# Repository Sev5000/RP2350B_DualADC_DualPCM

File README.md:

# RP2350B_DualADC_DualPCM
This is a PCB to neatly package a RP2350B, two AD9226 ADC PCBs and two PCM1802 audio boards for capture with hsdaoh.
Specifically designed to still be usefull without smds (no head switch input then). Through-hole soldering only works just fine.

For use with [https://github.com/steve-m/hsdaoh-rp2350/tree/pcm1802](https://github.com/steve-m/hsdaoh/tree/dual_12bit_adc)

Features:
- Two 12bit 40MS/s ADCs
- Four channel audio input all with a common clock
- No SMD soldering needed! Works fine just connecting breakout boards
- Socket for a Pimoroni PGA2350 and RP2350 and its periphery
- The protected head switch input has footprints for edge and horizontal SMA/SMB (SMD soldering needed)
- Socket for USB C and Micro B breakouts

Bill of material: 
- 1x This PCB (Send the Gerber .zip to JLC, PCBWay, ..)
- 1x Pimoroni PGA2350
- 2x AD9226: https://aliexpress.com/item/1005003038271519.html
- 2x PCM1802: https://aliexpress.com/item/1005006412873984.html
- 4x RCA-105 or RCA-106: https://aliexpress.com/item/1005006152724809.html
- 2x 9pin 2.54mm pin-socket header 
- 2x 2x10pin 2.54mm pin-socket header
- 2x 3pin 2.54mm pin header (remove the center pin for connecting R/L of the PCM1802)
- 2x 3pin 2.54mm pin-socket header (remove the center pin for connecting R/L of the PCM1802)
- 1x vertical 6mm push button: https://aliexpress.com/item/1005005831153897.html (horizontal soldered in vertical and a drop of glue for stability works as well)

No SMD variant:
- 1x Adafruit DVI breakout board
- 4x 2x8pin 2.54mm pin-socket header
- Either Adafruit USB Micro-B Breakout Board or Adafruit USB C Breakout Board

SMD Variant with PGA2350:
- Regular HDMI connector
- micro USB connector
- 8× 0402 270 ohm resistors
- 4x 0805 100nF ceramic capacitors
- For experimental EDID communication and HPD: 4x SOD123 3.3V Zener, 4x 0402 ~27 ohm resistors, 2x 0402 2k2 ohm resistors

For head switch input:
- 1x SOD123 3.3V zener diode
- 1x SOD123 standard diode
- 1x 0805 1k resistor
- 1x edge SMA/SMB or horizontal SMA/SMB and/or 2pin header

Notes:
- Soldering the RP2350B and its periphery might work but was not tested so far.
- The PCM1802 board needs MODE0 (MODE1 only with previous HSDAOH releases) bridged *and* connected to 3.3V with a wire (Those boards have a design error):
NOTE: Picture shows the configuration for the older firmware, now only MODE0 needs to be bridged and connected to 3.3V

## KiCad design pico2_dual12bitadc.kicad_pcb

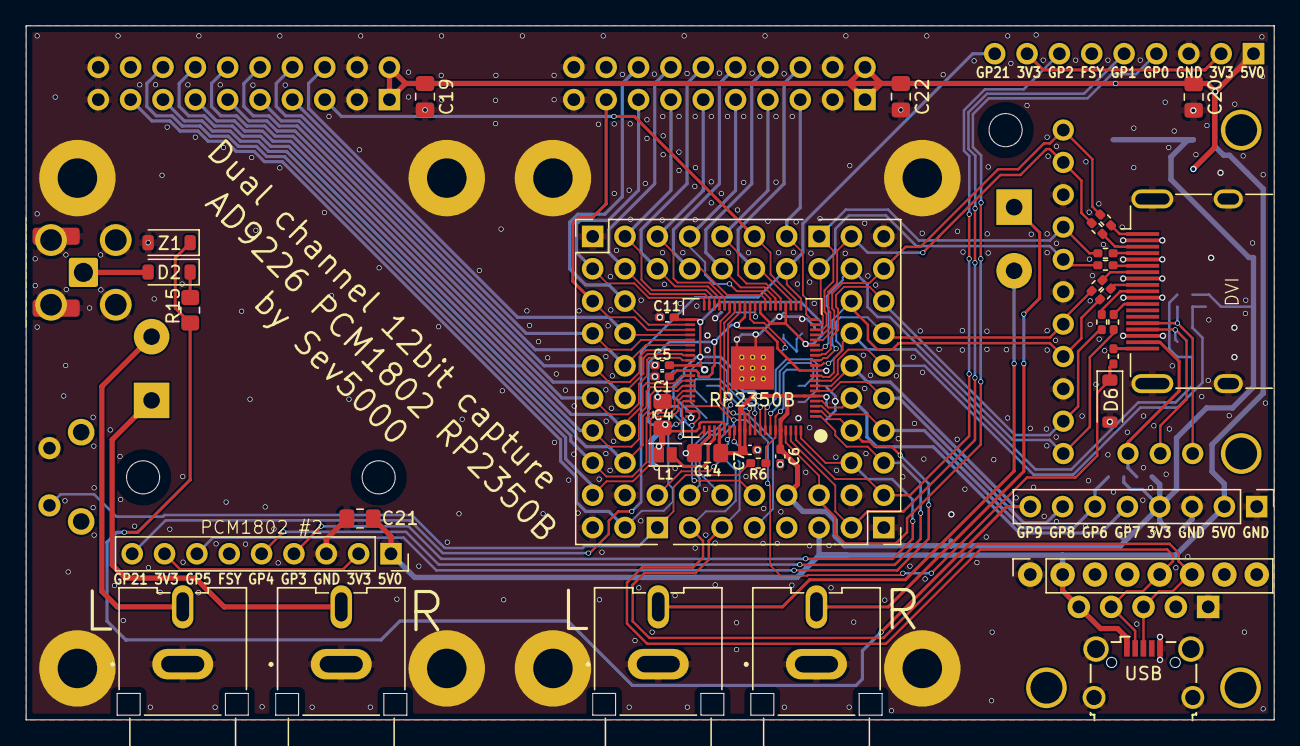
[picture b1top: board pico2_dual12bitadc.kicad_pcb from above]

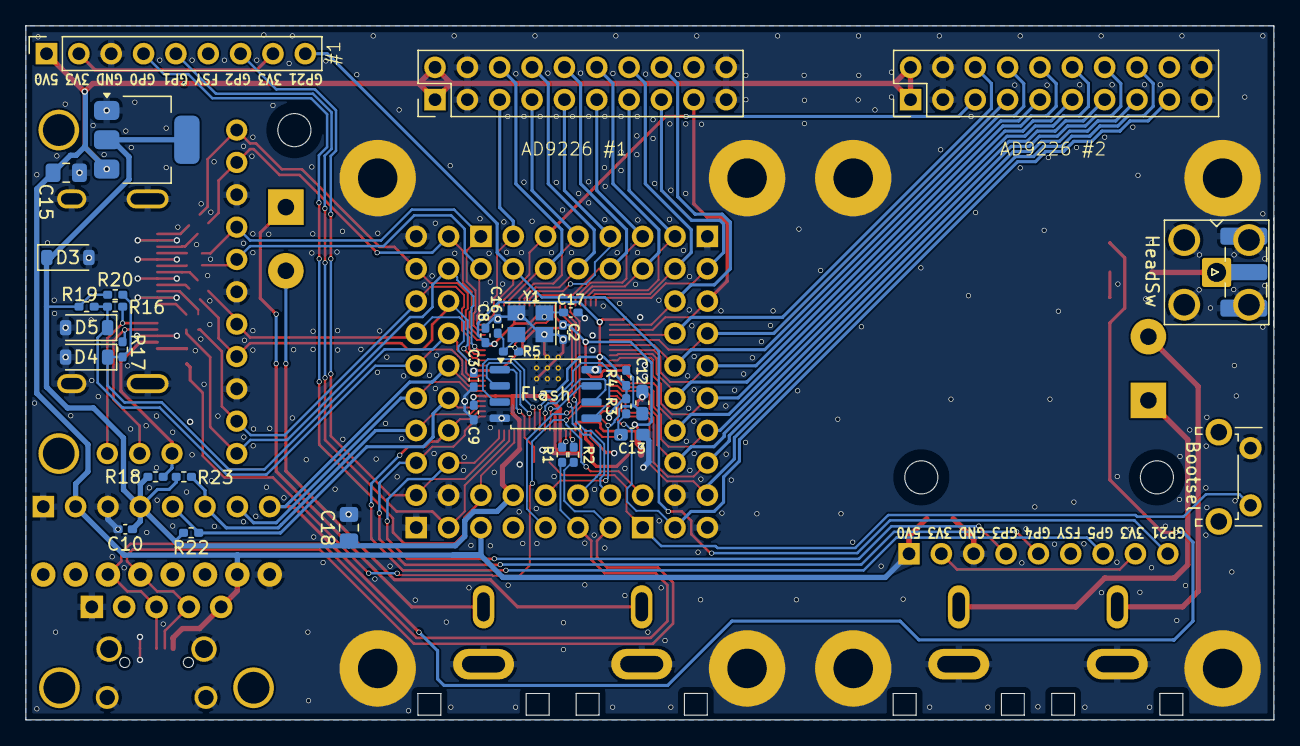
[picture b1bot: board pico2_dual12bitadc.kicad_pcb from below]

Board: 2 copper layers, 98.0 x 54.5 mm, 75 parts (34 on the bottom side), 89 nets.

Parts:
AD9226 #1: AD9226 #1; AD9226 PCB
AD9226 #2: AD9226 #2; AD9226 PCB
Bootsel: SW_Push; SW_Tactile_SPST_Angled_PTS645Vx58-2LFS
C1, C2, C3, C5, C6, C7, C8, C9, C10, C11: 100nF; C_0402_1005Metric_Pad0.74x0.62mm_HandSolder
C4, C14, C15: 10uF; C_0805_2012Metric_Pad1.18x1.45mm_HandSolder
C12, C13: 2.2uF; C_0603_1608Metric_Pad1.08x0.95mm_HandSolder
C16, C17: 15pF; C_0402_1005Metric_Pad0.74x0.62mm_HandSolder
C18: 4.7uF; C_0805_2012Metric_Pad1.18x1.45mm_HandSolder
C19, C20, C21, C22: 100nF; C_0805_2012Metric_Pad1.18x1.45mm_HandSolder
D2: D; D_SOD-123
D3, D4, D5, D6: D_Zener3.3V; D_SOD-123
DVI: DVI Breakout; Adafruit DVI Breakout
Flash: W25Q128JVS; SOIC-8_5.23x5.23mm_P1.27mm
GP9 GP8 GP6 GP7 3V3 GND 5V0 GND: Aux Connector; PinHeader_1x08_P2.54mm_Vertical
HeadSw: SMAEdge; SMA_Samtec_SMA-J-P-H-ST-EM1_EdgeMount
J1: PGA2350 Left; PinHeader_2x10_P2.54mm_Vertical
J2: PGA2350 Right; PinHeader_2x10_P2.54mm_Vertical
J3: PGA2350 Bottom; PinHeader_2x06_P2.54mm_Vertical
J4: PGA2350 Top; PinHeader_2x06_P2.54mm_Vertical
J6: HDMI_A; HDMI_A_Molex_208658-1001_Horizontal
J11: Adafruit USB-C and Micro Breakout; Adafruit USB C and Micro Breakout
J12: SMA90; SMA_Amphenol_901-143_Horizontal
L: L; CUI_RCJ-047
L1: 3.3uH; L_TDK_MLZ2012_h1.25mm
L#2: L; CUI_RCJ-047
PCM1802 #2: PCM1802 #2; PCM1802 PCB
R: R; CUI_RCJ-047
R1, R2, R3, R16, R17, R18, R21: 27R4; R_0402_1005Metric_Pad0.72x0.64mm_HandSolder
R4: 220; R_0402_1005Metric_Pad0.72x0.64mm_HandSolder
R5, R6: 1k; R_0402_1005Metric_Pad0.72x0.64mm_HandSolder
R7, R8, R9, R10, R11, R12, R13, R14: 270; R_0402_1005Metric_Pad0.72x0.64mm_HandSolder
R15: 1k; R_0805_2012Metric_Pad1.20x1.40mm_HandSolder
R19, R20, R22, R23: 2k2; R_0402_1005Metric_Pad0.72x0.64mm_HandSolder
R#2: R; CUI_RCJ-047
RP2350B: RP2350B-QFN80; RP2350B_QFN-80_EP_10.573x10.573_Pitch0.4mm
U1: NCP1117-3.3_SOT223; SOT-223-3_TabPin2
USB: USB_B_Micro; USB_Micro-B_Wuerth_629105150521_CircularHoles
Y1: ABM8-272-T3; Crystal_SMD_Abracon_ABM8G-4Pin_3.2x2.5mm
Z1: D_Zener3.3V; D_SOD-123

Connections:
+1V1: C1.1, C2.1, C3.1, C4.1, L1.2, RP2350B.10 (DVDD), RP2350B.32 (DVDD), RP2350B.51 (DVDD), RP2350B.65 (VREG_FB)
+3V3: C5.1, C6.1, C7.1, C8.1, C9.1, C10.1, C11.1, C14.1, C18.1, D3.1 (K), Flash.8 (VCC), GP9 GP8 GP6 GP7 3V3 GND 5V0 GND.4 (3V3), J4.10, R3.2, R4.1, R18.2, R19.2, R20.1, R22.2, R23.1, RP2350B.5 (IOVDD), RP2350B.15 (IOVDD), RP2350B.24 (IOVDD), RP2350B.29 (IOVDD), RP2350B.41 (IOVDD), RP2350B.50 (IOVDD), RP2350B.60 (IOVDD), RP2350B.64 (VREG_VIN), RP2350B.68 (USB_OTP_VDD), RP2350B.69 (QSPI_IOVDD), RP2350B.76 (IOVDD), U1.2 (VO)
/ADC VREF: C12.1, J4.8, R4.2, RP2350B.59 (ADC_AVDD)
/BOOTSEL: Bootsel.2, J4.1, R6.2
/CK+: DVI.10 (CK+), J1.15, R13.1, RP2350B.13 (GPIO14)
/CK-: DVI.12 (CK-), J1.18, R14.1, RP2350B.14 (GPIO15)
/D0+: DVI.7 (D0+), J1.13, R11.1, RP2350B.11 (GPIO12)
/D0-: DVI.9 (D0-), J1.16, R12.1, RP2350B.12 (GPIO13)
/D1+: DVI.4 (D1+), J3.1, R9.1, RP2350B.18 (GPIO18)
/D1-: DVI.6 (D1-), J3.2, R10.1, RP2350B.19 (GPIO19)
/D2+: DVI.1 (D2+), J1.17, R7.1, RP2350B.16 (GPIO16)
/D2-: DVI.3 (D2-), J1.20, R8.1, RP2350B.17 (GPIO17)
/GPIO0: J4.12, RP2350B.77 (GPIO0)
/GPIO1: J1.2, RP2350B.78 (GPIO1)
/GPIO2: J1.3, RP2350B.79 (GPIO2)
/GPIO3: J1.6, PCM1802 #2.4 (DOUT), RP2350B.80 (GPIO3)
/GPIO4: J1.5, PCM1802 #2.5 (BCK), RP2350B.1 (GPIO4)
/GPIO5: J1.8, PCM1802 #2.7 (LRCK), RP2350B.2 (GPIO5)
/GPIO6: GP9 GP8 GP6 GP7 3V3 GND 5V0 GND.6 (GP6/SDA), J1.7, R23.2, RP2350B.3 (GPIO6)
/GPIO7: GP9 GP8 GP6 GP7 3V3 GND 5V0 GND.5 (GP7/SCL), J1.10, R22.1, RP2350B.4 (GPIO7)
/GPIO8: GP9 GP8 GP6 GP7 3V3 GND 5V0 GND.7 (GP8), J1.9, RP2350B.6 (GPIO8)
/GPIO9: GP9 GP8 GP6 GP7 3V3 GND 5V0 GND.8 (GP9/HeadSw), J1.12, R15.2, RP2350B.7 (GPIO9), Z1.1 (K)
/GPIO10: D5.1 (K), J1.11, R16.1, R19.1, RP2350B.8 (GPIO10)
/GPIO11: D4.1 (K), J1.14, R17.1, R20.2, RP2350B.9 (GPIO11)
/GPIO20: AD9226 #1.5, J3.3, RP2350B.20 (GPIO20)
/GPIO21: J3.4, PCM1802 #2.9 (SCK), RP2350B.21 (GPIO21)
/GPIO22: AD9226 #2.5, J3.5, RP2350B.22 (GPIO22)
/GPIO23: AD9226 #1.6, J3.6, RP2350B.23 (GPIO23)
/GPIO24: AD9226 #1.7, J3.7, RP2350B.25 (GPIO24)
/GPIO25: AD9226 #1.8, J3.8, RP2350B.26 (GPIO25)
/GPIO26: AD9226 #1.9, J3.9, RP2350B.27 (GPIO26)
/GPIO27: AD9226 #1.10, J3.10, RP2350B.28 (GPIO27)
/GPIO28: AD9226 #1.11, J3.11, RP2350B.36 (GPIO28)
/GPIO29: AD9226 #1.12, J3.12, RP2350B.37 (GPIO29)
/GPIO30: AD9226 #1.13, J2.2, RP2350B.38 (GPIO30)
/GPIO31: AD9226 #1.14, J2.4, RP2350B.39 (GPIO31)
/GPIO32: AD9226 #1.15, J2.3, RP2350B.40 (GPIO32)
/GPIO33: AD9226 #1.16, J2.6, RP2350B.42 (GPIO33)
/GPIO34: AD9226 #1.17, J2.5, RP2350B.43 (GPIO34)
/GPIO35: AD9226 #2.6, J2.8, RP2350B.44 (GPIO35)
/GPIO36: AD9226 #2.7, J2.7, RP2350B.45 (GPIO36)
/GPIO37: AD9226 #2.8, J2.10, RP2350B.46 (GPIO37)
/GPIO38: AD9226 #2.9, J2.9, RP2350B.47 (GPIO38)
/GPIO39: AD9226 #2.10, J2.12, RP2350B.48 (GPIO39)
/GPIO40: AD9226 #2.11, J2.11, RP2350B.49 (GPIO40_ADC0)
/GPIO41: AD9226 #2.12, J2.14, RP2350B.52 (GPIO41_ADC1)
/GPIO42: AD9226 #2.13, J2.13, RP2350B.53 (GPIO42_ADC2)
/GPIO43: AD9226 #2.14, J2.16, RP2350B.54 (GPIO43_ADC3)
/GPIO44: AD9226 #2.15, J2.15, RP2350B.55 (GPIO44_ADC4)
/GPIO45: AD9226 #2.16, J2.17, RP2350B.56 (GPIO45_ADC5)
/GPIO46: AD9226 #2.17, J2.20, RP2350B.57 (GPIO46_ADC6)
/GPIO47: D6.1 (K), J4.2, R21.2, RP2350B.58 (GPIO47_ADC7)
/L: L1.1, RP2350B.63 (VREG_LX)
/RUN: J4.7, RP2350B.35 (RUN)
/SWCLK: J4.6, RP2350B.33 (SWCLK)
/SWDIO: J4.4, RP2350B.34 (SWDIO)
/USB_D+: J4.5, J11.6 (D+), R1.2, USB.3 (D+)
/USB_D-: J4.3, J11.5 (D-), R2.2, USB.2 (D-)
GND: AD9226 #1.3, AD9226 #1.4, AD9226 #1.19, AD9226 #1.20, AD9226 #2.3, AD9226 #2.4, AD9226 #2.19, AD9226 #2.20, Bootsel.1, C1.2, C2.2, C3.2, C4.2, C5.2, C6.2, C7.2, C8.2, C9.2, C10.2, C11.2, C12.2, C13.2, C14.2, C15.2, C16.1, C17.2, C18.2, C19.2, C20.2, C21.2, C22.2, D3.2 (A), D4.2 (A), D5.2 (A), D6.2 (A), DVI.17 (GND), Flash.4 (GND), GP9 GP8 GP6 GP7 3V3 GND 5V0 GND.1 (GND), GP9 GP8 GP6 GP7 3V3 GND 5V0 GND.3 (GND), HeadSw.2 (Ext), J1.1, J1.4, J1.19, J2.1, J2.18, J2.19, J6.2 (D2S), J6.5 (D1S), J6.8 (D0S), J6.11 (CKS), J6.17 (GND), J6.SH, J11.1 (GND), J12.2 (Ext), L.2 (Ext), L#2.2 (Ext), PCM1802 #2.3 (GND), R.2 (Ext), R#2.2 (Ext), RP2350B.62 (VREG_PGND), RP2350B.81 (GND), U1.1 (GND), USB.5 (GND), USB.6 (Shield), Y1.2, Y1.4, Z1.2 (A)
unnamed: C16.2, R5.2, Y1.3
unnamed: D2.2 (A), HeadSw.1 (In), J12.1 (In)
unnamed: D2.1 (K), R15.1
unnamed: J6.10 (CK+), R13.2
unnamed: J6.12 (CK-), R14.2
unnamed: J6.7 (D0+), R11.2
unnamed: J6.9 (D0-), R12.2
unnamed: J6.4 (D1+), R9.2
unnamed: J6.6 (D1-), R10.2
unnamed: J6.1 (D2+), R7.2
unnamed: J6.3 (D2-), R8.2
unnamed: PCM1802 #2.2 (3.3V), PCM1802 #2.8 (PDW)
unnamed: DVI.18 (+5V), J6.18 (+5V), R18.1
unnamed: J6.19 (HPD), R21.1
unnamed: DVI.15 (SCL), J6.15 (SCL), R16.2
unnamed: DVI.16 (SDA), J6.16 (SDA), R17.2
unnamed: PCM1802 #2.10 (Rin), R#2.1 (In)
unnamed: L.1 (In), PCM1802 #2.11 (Lin)
unnamed: Flash.6 (CLK), RP2350B.71 (QSPI_SCLK)
unnamed: Flash.5 (DI(IO0)), RP2350B.72 (QSPI_SD0)
unnamed: Flash.2 (DO(IO1)), RP2350B.74 (QSPI_SD1)
unnamed: Flash.3 (IO2), RP2350B.73 (QSPI_SD2)
unnamed: Flash.7 (IO3), RP2350B.70 (QSPI_SD3)
unnamed: Flash.1 (~CS), R6.1, RP2350B.75 (QSPI_SS)
unnamed: R2.1, RP2350B.66 (USB_DM)
unnamed: R1.1, RP2350B.67 (USB_DP)
unnamed: C13.1, R3.1, RP2350B.61 (VREG_AVDD)
unnamed: C17.1, RP2350B.30 (XIN), Y1.1
unnamed: R5.1, RP2350B.31 (XOUT)
VBUS: AD9226 #1.1, AD9226 #1.2, AD9226 #2.1, AD9226 #2.2, C15.1, C19.1, C20.1, C21.1, C22.1, GP9 GP8 GP6 GP7 3V3 GND 5V0 GND.2 (VBUS), J4.11, J11.2 (VBUS), PCM1802 #2.1 (5V), U1.3 (VI), USB.1 (VBUS)

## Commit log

2025-02-03 Initial upload
2025-03-30 Update README.md
    Change PCM config to match the latest HSDAOH release
2025-04-21 3D Printable Case
    - Added 3D printable case, with low profile variant for devices with removed bottom connector.
